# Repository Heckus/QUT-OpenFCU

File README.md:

# QUT Open Source Autopilot Hardware (QUTOpenFCU)

## 🏛️ University Property & Acknowledgement
**This project and its contents have been supported by the Queensland University of Technology (QUT)**. 
It was developed as an in-house hardware solution for UAV units at QUT. QUT acknowledges the Turrbal and Yugara, as the First Nations owners of the lands where QUT now stands. 

##  Project Overview
This project involves refactoring, building, programming, and testing an open-source flight module design to serve as a replacement for current hardware. The design stems from the pixracer design, produced by Nick Arsov and Phillip Kocmoud and architected by Lorenz Meier, David Sidrane and Leonard Hall.
(https://docs.px4.io/v1.12/en/flight_controller/pixracer.html)

The primary objective is to create an alternative to the difficult-to-source off-the-shelf Pixhawk 6. This work builds upon a edited pixracer version produced by KAI (Wesley) in 2022.

The final demonstrator capabilities include:
* Loading open-source firmware with customizations.
* Connecting to QGroundControl.
* Basic operations for manned flight on a simple airframe.
* Autonomous flight via ros2 and internal positioning system

##  Hardware Specifications & Modifications
The core design is based on the AUAV Pixracer, which is the FMUv4 generation of Pixhawk autopilots. 
* **Main System-on-Chip**: STM32F427VIT6 rev.3 CPU (180 MHz ARM Cortex® M4).
* **v2 Sensor Suite**: Invensense ICM-42688-p (Accel / Gyro), Invensense ICM-20608-G (Accel / Gyro), MS561101BA03-50 (Barometer), and LIS3MDLTR (Mag).
* **v2 Board Modifications**: The design includes small placement changes to the SD card, C, and R components. It also introduces new interfaces, including a Reset Button and a BOOT0 Button.

##  Firmware
* The PX4 firmware is loaded onto the STM chip using DFU.
* Small modifications were required for drivers and SPI chip select pins.
* Mavlink 8266 firmware was utilized for the external WiFi ESP-01 module.
* Custom firmware was also designed to test sensor communication, using the onboard LED to display different colors for different communication failures.

##  Current Issues & Future Work (v3 Development)
### Known Board Issues (v2)
* The D4 label is missing from the board.
* The labels are too small to read.
* There is no thermal relief on the ground pads, and the board name is out of date.
* The USB data lines are not the same length.
* One of the accelerometer sensors needs to be rotated 90 degrees.
* A breakout for serial debugging output needs to be added.
* The SD card footprint should be reversed for better access.
* The STM chip is not connected to 3.3v.
* Offboarding mode errors on QGroundControl 

### Future Work
* Fixing the outlined issues and setting up external production.
* Designing an outer case with proper sensor specs, including barometer foam protection and chip vibration isolation techniques.
* Validating external component connections, PX4 firmware, and QGroundControl configurations.
* Considering turning the design into a Pi header with required isolation.

## 📸 Project Showcase
Operation videos and development images can be found inside the Showcase folder
* 
* 
* 
* 
* 

##  Author Credentials
**Name:** Joshua Hecke
**Student ID:** n11585382
**Role:** Project Developer 

## 📄 License Disclaimer
The base AUAV Pixracer is an open hardware design licensed under the Creative Commons Attribution-ShareAlike 3.0 Unported (CC BY-SA 3.0) license.

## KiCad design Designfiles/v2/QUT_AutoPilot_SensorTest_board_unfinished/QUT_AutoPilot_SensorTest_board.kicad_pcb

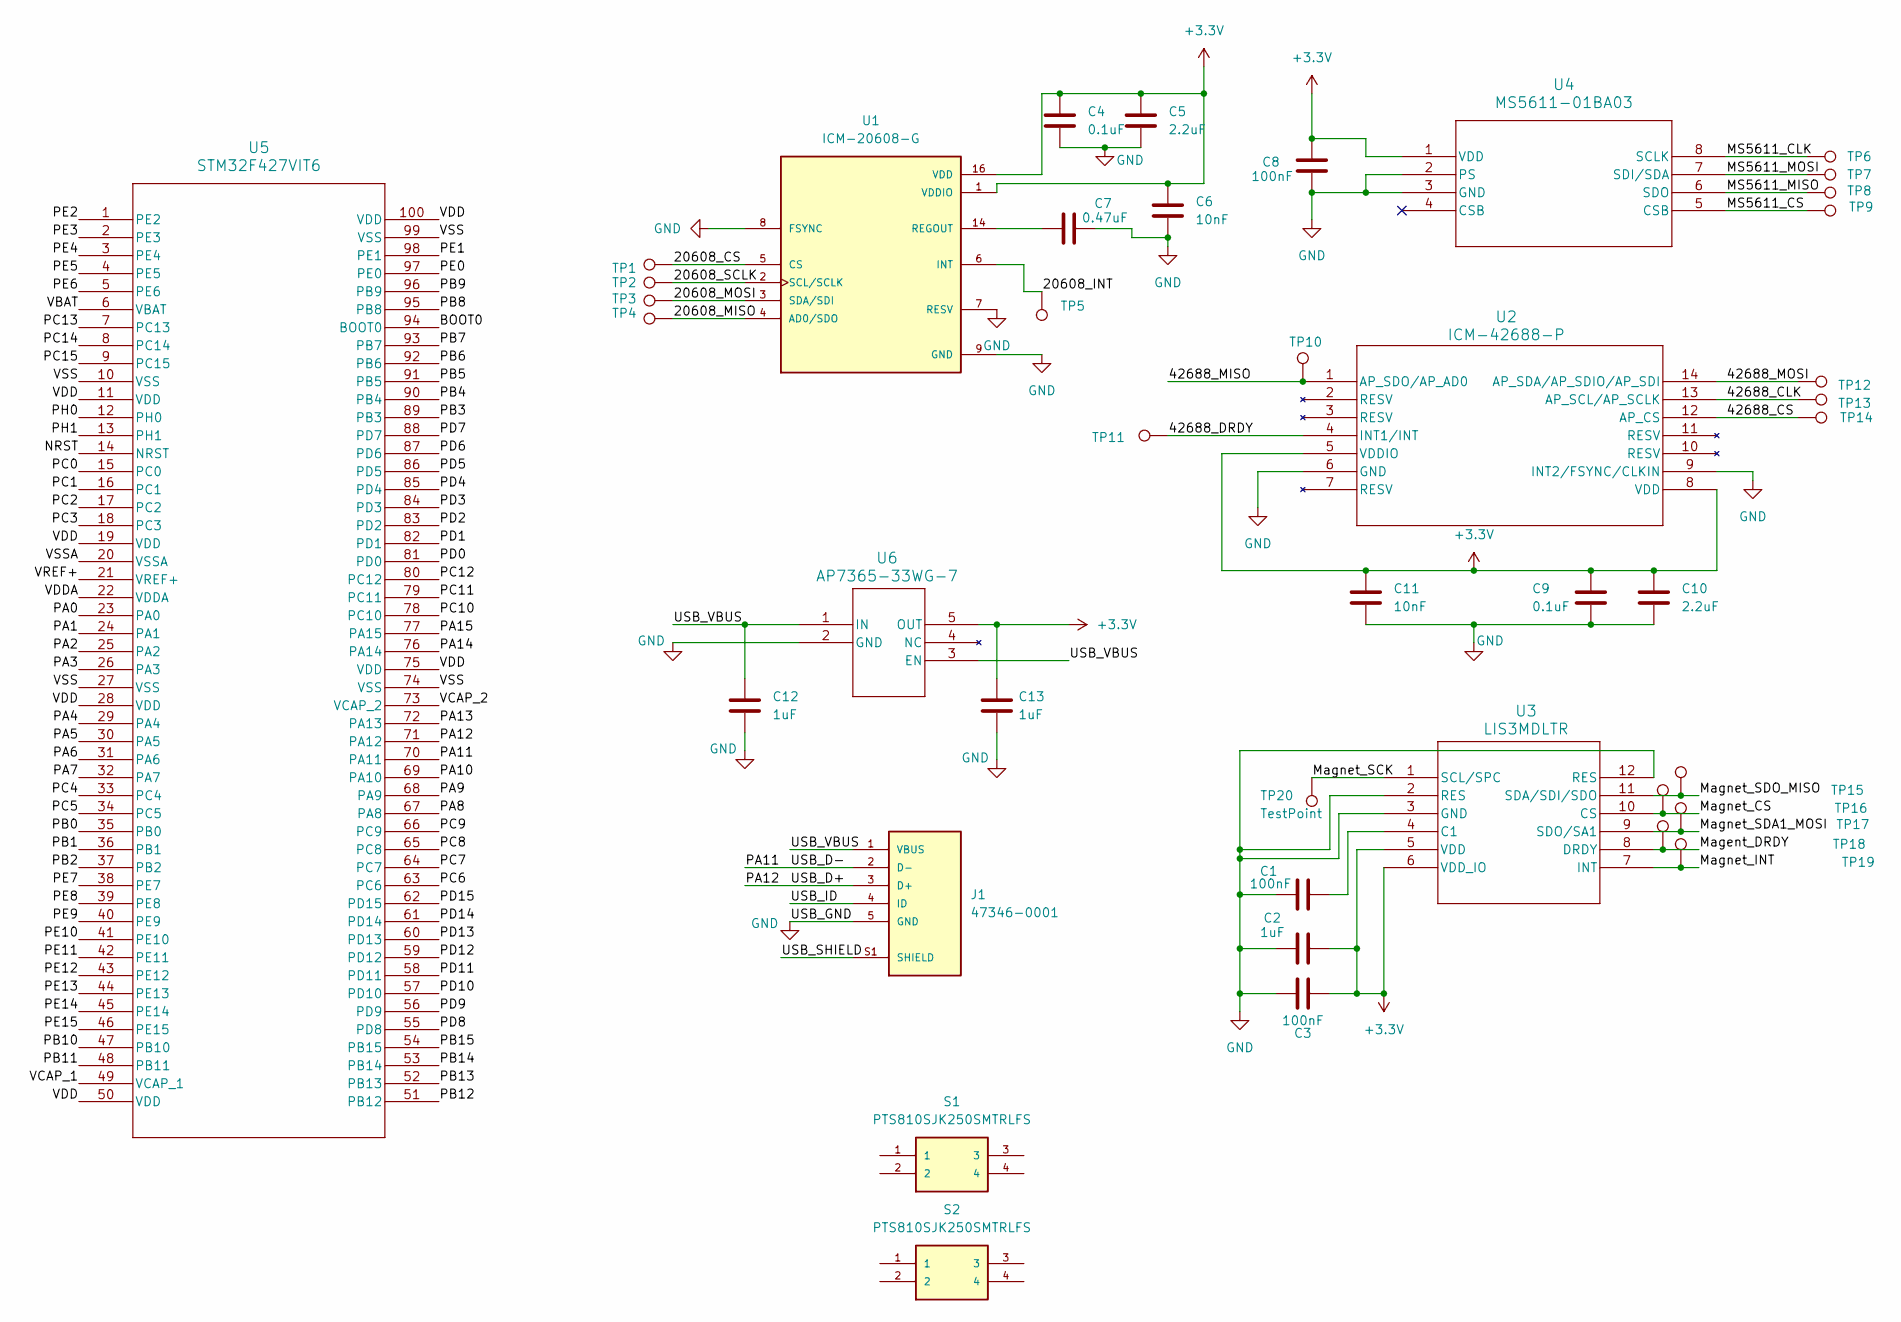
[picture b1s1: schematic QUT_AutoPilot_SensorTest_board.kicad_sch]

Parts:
C1, C3, C8: 100nF; C_0402_1005Metric
C2, C12, C13: 1uF; C_0402_1005Metric
C4, C9: 0.1uF; C_0402_1005Metric
C5, C10: 2.2uF; C_0402_1005Metric
C6, C11: 10nF; C_0402_1005Metric
C7: 0.47uF; C_0402_1005Metric
J1: 47346-0001; MOLEX_47346-0001; PARTREV E
S1, S2: PTS810SJK250SMTRLFS; PTS810SJG250SMTRLFS; MANUFACTURER_PART_NUMBER PTS810SJK250SMTRLFS
TP1, TP2, TP3, TP4, TP5, TP6, TP7, TP8, TP9, TP10, TP11, TP12, TP13, TP14, TP15, TP16, TP17, TP18, TP19, TP20: TestPoint; TestPoint_Keystone_5019_Miniature
U1: ICM-20608-G; PQFN50P300X300X80-16N; PARTREV 1.0
U2: ICM-42688-P; PQFN50P300X300X80-16N
U3: LIS3MDLTR; LGA-12_2X2X1_STM
U4: MS5611-01BA03; SON8_MS5611-01BA03_TEC
U5: STM32F427VIT6; LQFP100_14X14_STM
U6: AP7365-33WG-7; SOT25_DIO

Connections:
+3.3V: C2.2, C3.2, C4.1, C5.1, C6.1, C8.1, C9.1, C10.1, C11.1, C13.1, U1.1 (VDDIO), U1.16 (VDD), U2.5 (VDDIO), U2.8 (VDD), U3.5 (VDD), U3.6 (VDD_IO), U4.1 (VDD), U6.5 (OUT)
/20608_CS: TP1.1, U1.5 (CS)
/20608_INT: TP5.1, U1.6 (INT)
/20608_MISO: TP4.1, U1.4 (AD0/SDO)
/20608_MOSI: TP3.1, U1.3 (SDA/SDI)
/20608_SCLK: TP2.1, U1.2 (SCL/SCLK)
/42688_CLK: TP13.1, U2.13 (AP_SCL/AP_SCLK)
/42688_CS: TP14.1, U2.12 (AP_CS)
/42688_DRDY: TP11.1, U2.4 (INT1/INT)
/42688_MISO: TP10.1, U2.1 (AP_SDO/AP_AD0)
/42688_MOSI: TP12.1, U2.14 (AP_SDA/AP_SDIO/AP_SDI)
/BOOT0: U5.94 (BOOT0)
/MS5611_CLK: TP6.1, U4.8 (SCLK)
/MS5611_CS: TP9.1, U4.5 (CSB)
/MS5611_MISO: TP8.1, U4.6 (SDO)
/MS5611_MOSI: TP7.1, U4.7 (SDI/SDA)
/Magent_DRDY: TP18.1, U3.8 (DRDY)
/Magnet_CS: TP16.1, U3.10 (CS)
/Magnet_INT: TP19.1, U3.7 (INT)
/Magnet_SCK: TP20.1, U3.1 (SCL/SPC)
/Magnet_SDA1_MOSI: TP17.1, U3.9 (SDO/SA1)
/Magnet_SDO_MISO: TP15.1, U3.11 (SDA/SDI/SDO)
/NRST: U5.14 (NRST)
/PA0: U5.23 (PA0)
/PA1: U5.24 (PA1)
/PA2: U5.25 (PA2)
/PA3: U5.26 (PA3)
/PA4: U5.29 (PA4)
/PA5: U5.30 (PA5)
/PA6: U5.31 (PA6)
/PA7: U5.32 (PA7)
/PA8: U5.67 (PA8)
/PA9: U5.68 (PA9)
/PA10: U5.69 (PA10)
/PA11: J1.2 (D-), U5.70 (PA11)
/PA12: J1.3 (D+), U5.71 (PA12)
/PA13: U5.72 (PA13)
/PA14: U5.76 (PA14)
/PA15: U5.77 (PA15)
/PB0: U5.35 (PB0)
/PB1: U5.36 (PB1)
/PB2: U5.37 (PB2)
/PB3: U5.89 (PB3)
/PB4: U5.90 (PB4)
/PB5: U5.91 (PB5)
/PB6: U5.92 (PB6)
/PB7: U5.93 (PB7)
/PB8: U5.95 (PB8)
/PB9: U5.96 (PB9)
/PB10: U5.47 (PB10)
/PB11: U5.48 (PB11)
/PB12: U5.51 (PB12)
/PB13: U5.52 (PB13)
/PB14: U5.53 (PB14)
/PB15: U5.54 (PB15)
/PC0: U5.15 (PC0)
/PC1: U5.16 (PC1)
/PC2: U5.17 (PC2)
/PC3: U5.18 (PC3)
/PC4: U5.33 (PC4)
/PC5: U5.34 (PC5)
/PC6: U5.63 (PC6)
/PC7: U5.64 (PC7)
/PC8: U5.65 (PC8)
/PC9: U5.66 (PC9)
/PC10: U5.78 (PC10)
/PC11: U5.79 (PC11)
/PC12: U5.80 (PC12)
/PC13: U5.7 (PC13)
/PC14: U5.8 (PC14)
/PC15: U5.9 (PC15)
/PD0: U5.81 (PD0)
/PD1: U5.82 (PD1)
/PD2: U5.83 (PD2)
/PD3: U5.84 (PD3)
/PD4: U5.85 (PD4)
/PD5: U5.86 (PD5)
/PD6: U5.87 (PD6)
/PD7: U5.88 (PD7)
/PD8: U5.55 (PD8)
/PD9: U5.56 (PD9)
/PD10: U5.57 (PD10)
/PD11: U5.58 (PD11)
/PD12: U5.59 (PD12)
/PD13: U5.60 (PD13)
/PD14: U5.61 (PD14)
/PD15: U5.62 (PD15)
/PE0: U5.97 (PE0)
/PE1: U5.98 (PE1)
/PE2: U5.1 (PE2)
/PE3: U5.2 (PE3)
/PE4: U5.3 (PE4)
/PE5: U5.4 (PE5)
/PE6: U5.5 (PE6)
/PE7: U5.38 (PE7)
/PE8: U5.39 (PE8)
/PE9: U5.40 (PE9)
/PE10: U5.41 (PE10)
/PE11: U5.42 (PE11)
/PE12: U5.43 (PE12)
/PE13: U5.44 (PE13)
/PE14: U5.45 (PE14)
/PE15: U5.46 (PE15)
/PH0: U5.12 (PH0)
/PH1: U5.13 (PH1)
/USB_ID: J1.4 (ID)
/USB_SHIELD: J1.S1 (SHIELD), J1.S2 (SHIELD), J1.S3 (SHIELD), J1.S4 (SHIELD), J1.S5 (SHIELD), J1.S6 (SHIELD)
/USB_VBUS: C12.1, J1.1 (VBUS), U6.1 (IN), U6.3 (EN)
/VBAT: U5.6 (VBAT)
/VCAP_1: U5.49 (VCAP_1)
/VCAP_2: U5.73 (VCAP_2)
/VDD: U5.11 (VDD), U5.19 (VDD), U5.28 (VDD), U5.50 (VDD), U5.75 (VDD), U5.100 (VDD)
/VDDA: U5.22 (VDDA)
/VREF+: U5.21 (VREF+)
/VSS: U5.10 (VSS), U5.27 (VSS), U5.74 (VSS), U5.99 (VSS)
/VSSA: U5.20 (VSSA)
GND: C1.1, C2.1, C3.1, C4.2, C5.2, C6.2, C7.2, C8.2, C9.2, C10.2, C11.2, C12.2, C13.2, J1.5 (GND), U1.7 (RESV), U1.8 (FSYNC), U1.9 (GND), U1.10 (GND), U1.11 (GND), U1.12 (GND), U1.13 (GND), U1.15 (GND), U2.6 (GND), U2.9 (INT2/FSYNC/CLKIN), U3.2 (RES), U3.3 (GND), U3.12 (RES), U4.2 (PS), U4.3 (GND), U6.2 (GND)
unnamed: C7.1, U1.14 (REGOUT)
unnamed: C1.2, U3.4 (C1)

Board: 2 copper layers, 40 parts (0 on the bottom side), 30 nets, no tracks yet.

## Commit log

2026-03-13 add:All files added
2026-03-13 edit:added credit to original designers in README
2026-03-13 edit:modified name in readme
2026-03-16 edit:handover
2026-03-16 edit: readme
